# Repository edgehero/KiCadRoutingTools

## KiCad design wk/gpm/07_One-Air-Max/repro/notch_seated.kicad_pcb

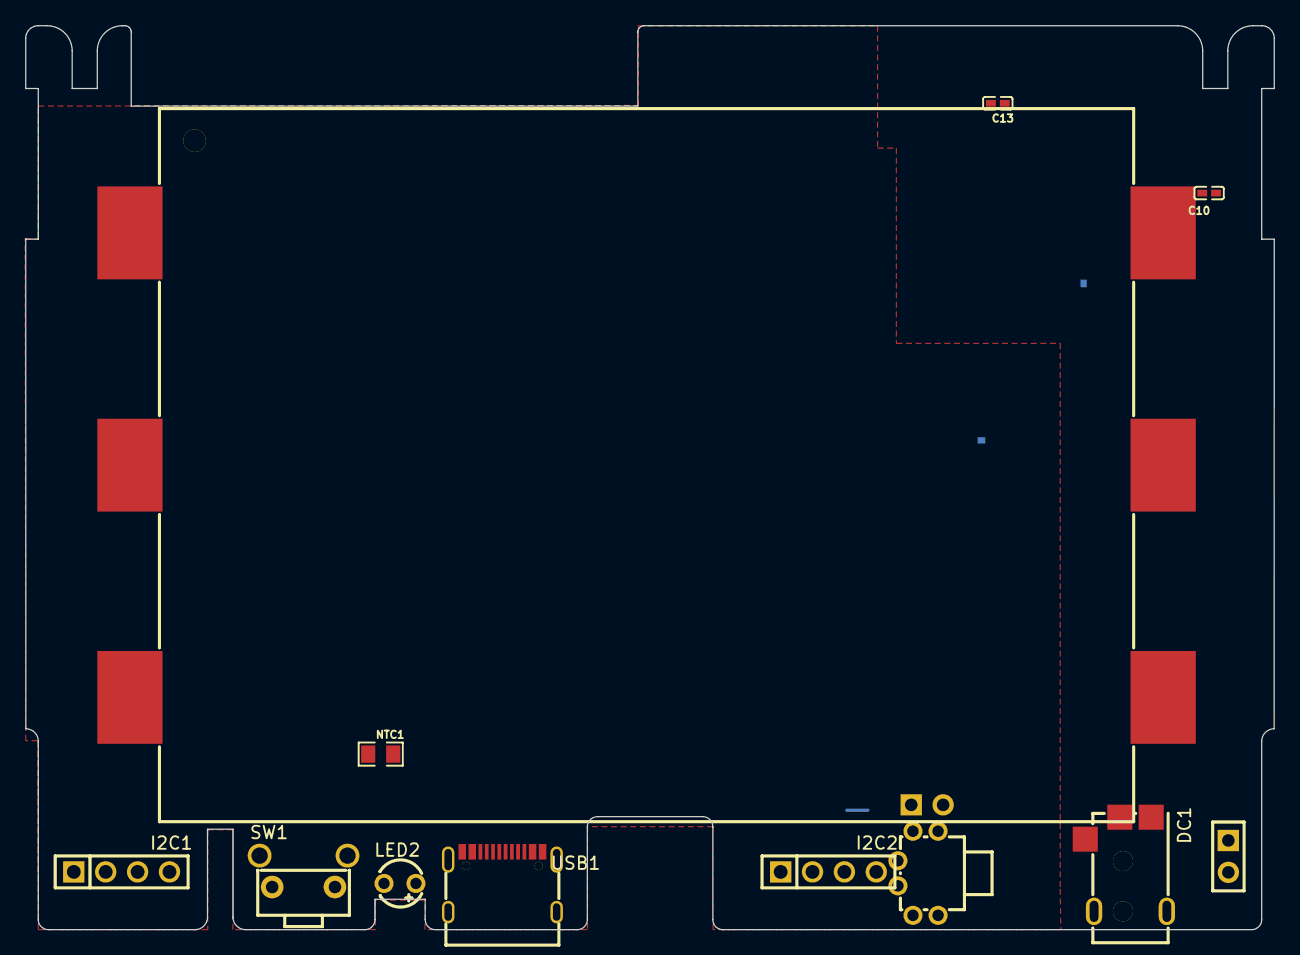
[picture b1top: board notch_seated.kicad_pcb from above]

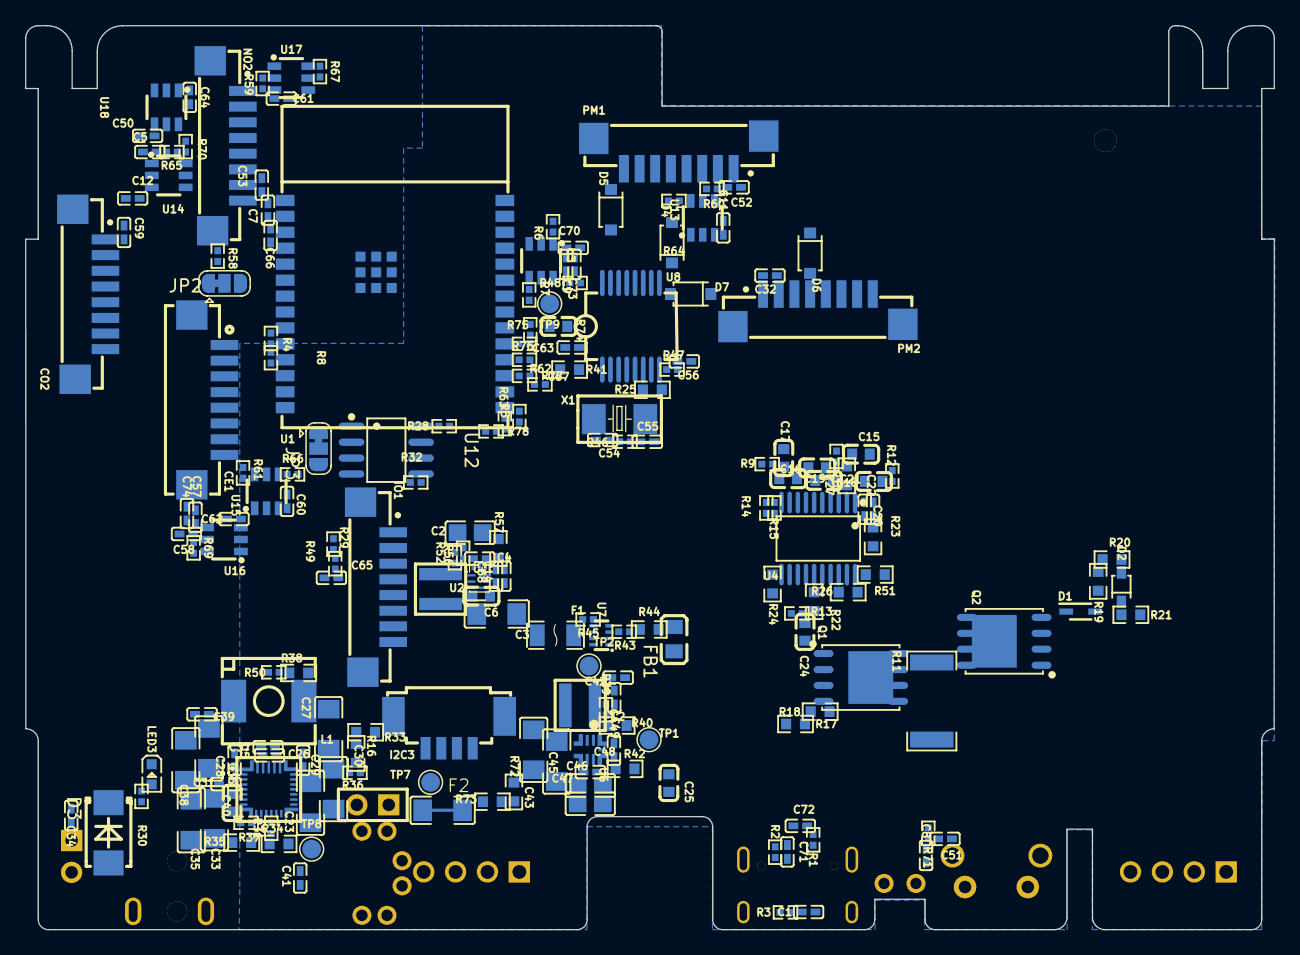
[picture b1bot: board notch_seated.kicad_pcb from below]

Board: 4 copper layers, 99.5 x 72.0 mm, 204 parts (192 on the bottom side), 120 nets, no tracks yet.

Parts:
BAT1: BH-18650-B5BA016; BAT-SMD_BH-18650-B5BA016
Battery1: ZX-PM2.54-1-2PY; HDR-TH_2P-P2.54-V-F
C1, C5, C7, C9, C10, C11, C12, C13, C26, C31, C34, C37, C39, C42, C44, C47, C50, C51, C52, C53, C56, C63, C65, C70: 0.1uF; C0402
C2: 10uF/25V; C0805
C3: 22uF/16V; C1206
C4, C49: 3.3nF; C0402
C6: 22uF; C0603
C8: 10nF; C0402
C14, C57, C58, C68, C74: 22uF; C0402
C15, C16, C17, C18, C19, C21, C24, C25: 0.1uF/50V; C0603
C20, C22: 1uF/50V; C0402
C23, C27, C30, C33, C35, C38, C40, C43, C45: 10uF; C1206
C28, C29: 47nF; C0402
C32, C59, C60, C61, C62, C64: 2.2uF; C0402
C36: 4.7uF; C0603
C41, C71, C72: 1nF; C0402
C46, C48: 22uF; C0805
C54, C55: 22pF_NM; C0402
C66, C73: 1uF; C0402
C67: 500pF; C0603
CE1: HC-1.25-8PWT; CONN-SMD_HC-1.25-8PWT
CO2: HC-1.25-8PLT; CONN-SMD_8P-P1.25_HC-1.25-8PLT
D1: BAS16J_135; SOD2512X80N
D2: MMSZ5246BS-7-F; SOD-323_L1.8-W1.3-LS2.5-RD
D3: SMBJ24A_C908801; SMB_L4.4-W3.6-LS5.3-RD
D4, D5, D6, D7: B5817W_C7420328; SOD-123_L2.7-W1.6-LS3.7-FD
DC1: DC-045A-13A; DC-IN-SMD_DC-045A-13A
F1: 2A-16V; F1206
F2: Fuse 5A; PCB_fuse
FB1: PBY201209T-601Y-N; L0805
I2C1, I2C2: Conn_01x04; HDR-TH_4P-P2.54-V-F
I2C3: 1.25-4PWB; CONN-SMD_1.25-4PWB
IO1: HC-1.25-8PLT; CONN-SMD_8P-P1.25_HC-1.25-8PLT
JP2, JP3: SolderJumper_3_Bridged12; SolderJumper-3_P1.3mm_Bridged12_RoundedPad1.0x1.5mm
L1: SPM6530T-1R0M120; IND-SMD_L7.1-W6.5-P5.60
L2: XGL4020-102MEC; IND-SMD_L4.0-W4.0_XAL4030-332MEC
L3: YSMC0420V-1R0M; IND-SMD_L4.0-W4.0_XGL4020
LED2: XL-304UBC; LED-TH_BD3.8-P2.54-FD_BLUE
LED3: FC-DA1608HRK-620D; LED0603-RD_RED
NO2: HC-1.25-8PLT; CONN-SMD_8P-P1.25_HC-1.25-8PLT
NTC1: KNTC0805/10KF3950; R0805
PM1, PM2: HC-1.25-8PLT; CONN-SMD_8P-P1.25_HC-1.25-8PLT
PWR_SW1: TK-6580A8-1; SW-TH_TK-6580A8-1
Q1, Q2: CSD18534Q5A; PQFN-8_L5.8-W4.9-P1.27-LS6.0-BL
R1, R2, R48: 5.1K; R0402
R3, R6, R31, R37: 100K; R0402
R4, R5, R8, R28, R29, R30, R32, R45, R47, R49, R50, R58, R59, R60, R61, R64, R65, R66, R67, R69, R70, R74, R75, R76, R77, R78: 10K; R0402
R7: 51K; R0402
R9, R12, R14, R15: 1K; R0402
R10, R13, R36: 100; R0402
R11: 10m / 1W; R2512
R16: 10.5K; R0603
R17, R19: 5.1K; R0603
R18: 10M; R0603
R20: 1M; R0603
R21: 3M; R0603
R22: 10K; R0603
R23, R25, R26, R27, R33, R41, R51, R72, R73: 0; R0603
R24: 470K; R0603
R34: 5.23K; R0603
R35: 255K; R0603
R38: 30.1K; R0603
R39: 200K; R0402
R40: 27K; R0603
R42, R57: 7.15K; R0603
R43: 16.9K; R0402
R44: 5K; R0603
R46: 1M; R0402
R52: 113k; R0402
R56: 24.9k; R0402
R62, R63: 22; R0402
R71: 210; R0402
SW1: TS-1096-A1B2-D2; KEY-TH_TS-1096-A1B2-D2
Solarpower1: ZX-PM2.54-1-2PY; HDR-TH_2P-P2.54-V-F
TP1, TP2, TP7, TP8, TP9: T_PG; TestPoint_Pad_D1.5mm
U1: ESP32-C6-WROOM-1-N8; WIRELM-SMD_ESP32-C6-WROOM-1
U2: TPS62902RPJR; VQFN-HR-9_L2.0-W1.5-P0.50-TL
U3: TPL5010DDCR; SOT-23-6_L2.9-W1.6-P0.95-LS2.8-BR
U4: BQ7790512PWR; TSSOP-20_L6.5-W4.4-P0.65-LS6.4-BL
U5: BQ25672RQMR; VQFN-29_L4.0-W4.0-P0.40-BL
U6: TPS62903QRYTRQ1_C20345985; VQFNHR-9_L2.2-W2.0_TPS62993QRYTRQ1
U7: TPS2117DRLR_C22399676; SOT-583-8_L2.1-W1.2-P0.50-LS1.6-BL
U8: WK2132-ISSG; SSOP-16_L7.2-W5.3-P0.65-LS7.8-BL
U12: AT24CM02-SSHD-B; SOIC-8_L4.9-W3.9-P1.27-LS6.0-BL
U13, U14, U15, U16, U17, U18: TPS27081ADDCR; SOT-23-6_L2.9-W1.6-P0.95-LS2.8-BR
USB1: GT-USB-7010ASV; USB-C-SMD_G-SWITCH_GT-USB-7010ASV
X1: SMD-5032_2P 14.7456MHZ 20PF 20PPM; OSC-SMD_L5.0-W3.2

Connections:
+3V3: C3.2, C6.2, C7.2, C9.1, C10.2, C13.2, C53.2, C63.2, C65.2, C66.2, C70.2, C73.2, I2C1.1, I2C2.1, I2C3.1, IO1.3, L3.1, R4.2, R5.2, R6.1, R8.2, R28.2, R29.2, R32.2, R47.2, R48.1, R49.2, R52.2, R66.2, R67.2, R74.2, R75.2, R76.2, R77.2, R78.2, U1.2 (3V3), U2.3 (VOS), U3.1 (VDD), U8.1 (VCC), U12.8 (VCC), U15.4 (VIN), U17.4 (VIN)
+5V: C2.1, C5.2, C14.2, C50.2, C57.2, C58.2, C68.2, C74.2, F1.1, IO1.1, R45.2, R64.2, R65.2, R69.2, R70.2, U2.5 (EN), U2.6 (VIN), U13.4 (VIN), U14.4 (VIN), U16.4 (VIN), U18.4 (VIN)
+5VBAT: C42.2, C43.2, C44.2, C45.2, L2.1, R39.2, U6.3 (VOS), U7.6 (VIN2)
+5VUSB: R43.2, U7.3 (VIN1), U7.5 (MODE), USB1.A4B9 (VBUS), USB1.B4A9 (VBUS)
/A0: R25.1, U8.6 (MP1)
/A1: R41.1, U8.4 (MP3)
/BOOT: C8.2, R5.1, SW1.1, U1.15 (IO9)
/Battery_holder/AVDD: C22.2, R23.2, U4.2 (AVDD)
/Battery_holder/BAT1: BAT1.2, BAT1.4, R9.1
/Battery_holder/BAT2: BAT1.3, BAT1.5, R12.1
/Battery_holder/BAT_TH: NTC1.2, R22.1, U4.15 (TS)
/Battery_holder/CHG: R19.2, U4.13 (CHG)
/Battery_holder/CTRC: R26.1, U4.18 (CTRC)
/Battery_holder/CTRD: R27.2, U4.19 (CTRD)
/Battery_holder/DSG: R17.2, U4.11 (DSG)
/Battery_holder/LD: R24.2, U4.14 (LD)
/Battery_holder/SRN: C17.1, C19.2, R13.2, U4.10 (SRN)
/Battery_holder/SRP: C15.2, C17.2, R10.2, U4.9 (SRP)
/Battery_holder/VBAT+: BAT1.6, C25.2, PWR_SW1.4, PWR_SW1.6, R14.1, R15.1
/EN: C67.2, R6.2, TP9.1, U1.3 (EN), U3.6 (RSTn)
/EN_CE: CE1.5, R61.2, U1.23 (IO15), U15.5 (ON/OFF), U16.5 (ON/OFF)
/EN_CO2: R58.2, U1.5 (IO5), U14.5 (ON/OFF)
/EN_NO2: R59.2, U1.4 (IO4), U17.5 (ON/OFF), U18.5 (ON/OFF)
/EN_PM: R60.2, U1.26 (IO3), U13.5 (ON/OFF)
/I2C_~RST: C56.2, R47.1, U8.8 (#RSTN)
/IO18: IO1.6, R78.1, U1.16 (IO18)
/IO19: IO1.5, R77.1, U1.17 (IO19)
/IO20: IO1.4, R76.1, U1.18 (IO20)
/IO21: CE1.6, R75.1, U1.19 (IO21)
/IO22: R74.1, U1.20 (IO22)
/IO23: CE1.4, R8.1, U1.21 (IO23)
/LED: R71.2, U1.11 (IO10)
/PM1_RXD: D5.2 (K), PM1.5
/PM1_TXD: D4.1 (A), PM1.4
/PM2_RXD: D7.2 (K), PM2.5
/PM2_TXD: D6.1 (A), PM2.4
/PR1: R43.1, R44.2, U7.4 (PR1)
/RX_CE: JP3.1 (A), U1.24 (RXD0)
/RX_CO2: CO2.5, U1.8 (IO0)
/SCL: I2C1.3, I2C2.3, I2C3.3, IO1.7, JP2.3 (B), NO2.7, R28.1, R32.1, U1.6 (IO6), U5.14 (SCL), U8.5 (MP2), U12.6 (SCL)
/SCL_TXD: CE1.7, JP2.2 (C)
/SDA: I2C1.4, I2C2.4, I2C3.4, IO1.8, JP3.3 (B), NO2.8, R29.1, R49.1, U1.7 (IO7), U5.15 (SDA), U8.7 (MP0), U12.5 (SDA)
/SDA_RXD: CE1.8, JP3.2 (C)
/Solar_module/BTST1: C28.2, U5.4 (BTST1)
/Solar_module/BTST2: C29.2, U5.19 (BTST2)
/Solar_module/FB/VSET: R39.1, R40.2, TP2.1, U6.9 (FB/VSET)
/Solar_module/ILIM_HIZ: R35.2, R37.2, U5.17 (ILIM_HIZ)
/Solar_module/PROG: R16.2, U5.20 (PROG)
/Solar_module/REGN: C36.2, R34.1, R35.1, U5.5 (REGN)
/Solar_module/SW1: C28.1, L1.1, U5.28 (SW1)
/Solar_module/SW2: C29.1, L1.2, U5.26 (SW2)
/Solar_module/SYS: C26.2, C27.2, R72.1, TP7.1, U5.25 (SYS)
/Solar_module/Solar+: C31.2, C33.2, C34.2, C35.2, D3.1, DC1.1, R30.1, Solarpower1.1, U5.2 (VBUS), U5.3 (VBUS), U5.8 (VAC2), U5.9 (VAC1)
/Solar_module/VBAT: Battery1.1, C23.2, C30.2, F2.1, R36.2, R73.1, TP8.1, U5.22 (BAT), U5.23 (BAT)
/TX_CE: JP2.1 (A), U1.25 (TXD0)
/TX_CO2: CO2.4, U1.9 (IO1)
/USB+: R63.2, U1.14 (IO13)
/USB-: R62.2, U1.13 (IO12)
/USB_D+: C71.2, R63.1, USB1.A6 (DP1), USB1.B6 (DP2)
/USB_D-: C72.2, R62.1, USB1.A7 (DN1), USB1.B7 (DN2)
/VMUX: F1.2, U7.2 (VOUT), U7.7 (VOUT)
/VOUT1: C11.2, C32.2, C52.2, PM1.1, PM2.1, U13.2 (VOUT), U13.3 (VOUT)
/VOUT2: C12.2, C59.2, CO2.1, U14.2 (VOUT), U14.3 (VOUT)
/VOUT3: C60.2, CE1.3, U15.2 (VOUT), U15.3 (VOUT)
/VOUT4: C62.2, CE1.1, U16.2 (VOUT), U16.3 (VOUT)
/VOUT5: C61.2, NO2.3, U17.2 (VOUT), U17.3 (VOUT)
/VOUT6: C64.2, NO2.1, U18.2 (VOUT), U18.3 (VOUT)
/WD_RST: U1.27 (IO2), U3.4 (DONE)
BAT-: BAT1.1, C15.1, C16.1, C18.1, C19.1, C20.1, C21.1, C22.1, NTC1.1, R10.1, R11.1, R26.2, R27.1, R51.1, U4.8 (AVSS), U4.20 (DVSS)
GND: C1.1, C2.2, C3.1, C4.1, C5.1, C6.1, C7.1, C8.1, C9.2, C10.1, C11.1, C12.1, C13.1, C14.1, C32.1, C50.1, C51.1, C52.1, C53.1, C54.1, C55.1, C56.1, C57.1, C58.1, C59.1, C60.1, C61.1, C62.1, C63.1, C64.1, C65.1, C66.1, C67.1, C68.1, C70.1, C71.1, C72.1, C73.1, C74.1, CE1.2, CE1.9, CE1.10, CO2.2, CO2.10, FB1.1, I2C1.2, I2C2.2, I2C3.2, I2C3.5, IO1.2, IO1.9, IO1.10, LED2.2 (K), NO2.2, NO2.9, NO2.10, PM1.2, PM1.10, PM2.2, PM2.9, PM2.10, R1.1, R2.1, R3.1, R7.1, R25.2, R41.2, R44.1, R56.1, R57.1, R58.1, R59.1, R60.1, R61.1, SW1.2, U1.1 (GND), U1.28 (GND), U1.29 (GND), U1.30 (GND), U1.31 (GND), U1.32 (GND), U1.33 (GND), U1.34 (GND), U1.35 (GND), U1.36 (GND), U1.37 (GND), U2.4 (GND), U3.2 (GND), U7.1 (GND), U8.12 (GND), U8.13 (MD0), U12.3 (A2), U12.4 (GND), U12.7 (WP), U13.1 (R2), U14.1 (R2), U15.1 (R2), U16.1 (R2), U17.1 (R2), U18.1 (R2), USB1.A1B12 (GND), USB1.B1A12 (GND)
unnamed: C1.2, R3.2, USB1.1 (SHELL), USB1.2 (SHELL), USB1.3 (SHELL), USB1.4 (SHELL)
unnamed: C24.2, Q1.1 (S), Q1.2 (S), Q1.3 (S), R11.2, R13.1, R18.1
unnamed: D1.2, R19.1, R20.2
unnamed: D1.1, D2.1 (K), Q2.4 (G), R20.1, R21.2
unnamed: D4.2 (K), U8.15 (TX1)
unnamed: D5.1 (A), U8.16 (RX1)
unnamed: D6.2 (K), U8.10 (TX2)
unnamed: D7.1 (A), U8.11 (RX2)
unnamed: F2.2, PWR_SW1.2, PWR_SW1.5
unnamed: C51.2, LED2.1 (A), R71.1
unnamed: LED3.2 (A), R30.2
unnamed: LED3.1 (K), U5.1 (STAT)
unnamed: Q1.5 (D), Q1.6 (S), Q1.7 (S), Q1.8 (S), Q2.5 (D), Q2.6 (S), Q2.7 (S), Q2.8 (S)
unnamed: Q1.4 (G), R17.1, R18.2
unnamed: R16.1, R33.1
unnamed: R4.1, U1.10 (IO8)
unnamed: R52.1, R56.2, U2.9 (FB/VSET)
unnamed: R57.2, U2.7 (MODE/S-CONF)
unnamed: C4.2, U2.8 (SS/TR)
unnamed: L3.2, U2.2 (SW)
unnamed: R7.2, U3.3 (DELAY/M_RST)
unnamed: R23.1, R51.2, U4.17 (CCFG)
unnamed: C16.2, R9.2, U4.7 (VC1)
unnamed: C18.2, R12.2, U4.6 (VC2)
unnamed: C21.2, R15.2, U4.3 (VC5), U4.4 (VC4), U4.5 (VC3)
unnamed: C20.2, R14.2, U4.1 (VDD)
unnamed: R22.2, U4.16 (VTB)
unnamed: R36.1, U5.18 (BATP)
unnamed: R31.1, U5.13 (CE)
unnamed: C37.2, C38.2, C39.2, C40.2, U5.29 (PMID)
unnamed: C41.1, U5.24 (SDRV)
unnamed: R34.2, R38.1, R50.2, U5.16 (TS)
unnamed: C46.2, C47.2, C48.2, R72.2, R73.2, U6.5 (EN), U6.6 (VIN)
unnamed: R42.2, U6.7 (MODE/S-CONF)
unnamed: TP1.1, U6.1 (PG)
unnamed: C49.2, U6.8 (SS/TR)
unnamed: L2.2, U6.2 (SW)
unnamed: R45.1, U7.8 (ST)
unnamed: R48.2, U8.9 (#IRQ)
unnamed: C54.2, R46.2, U8.2 (OSCI), X1.2 (OSC2)
unnamed: C55.2, R46.1, U8.3 (OSCO), X1.1 (OSC1)
unnamed: R64.1, U13.6 (R1/C1)
unnamed: R65.1, U14.6 (R1/C1)
unnamed: R66.1, U15.6 (R1/C1)
unnamed: R69.1, U16.6 (R1/C1)
unnamed: R67.1, U17.6 (R1/C1)
unnamed: R70.1, U18.6 (R1/C1)
unnamed: R1.2, USB1.A5 (CC1)
unnamed: R2.2, USB1.B5 (CC2)
PGND: Battery1.2, C23.1, C24.1, C25.1, C26.1, C27.1, C30.1, C31.1, C33.1, C34.1, C35.1, C36.1, C37.1, C38.1, C39.1, C40.1, C41.2, C42.1, C43.1, C44.1, C45.1, C46.1, C47.1, C48.1, C49.1, D2.2 (A), D3.2, DC1.2, DC1.3, DC1.4, FB1.2, Q2.1 (S), Q2.2 (S), Q2.3 (S), R21.1, R24.1, R31.2, R33.2, R37.1, R38.2, R40.1, R42.1, R50.1, Solarpower1.2, U5.10 (ACDRV2), U5.11 (ACDRV1), U5.27 (GND), U6.4 (GND)

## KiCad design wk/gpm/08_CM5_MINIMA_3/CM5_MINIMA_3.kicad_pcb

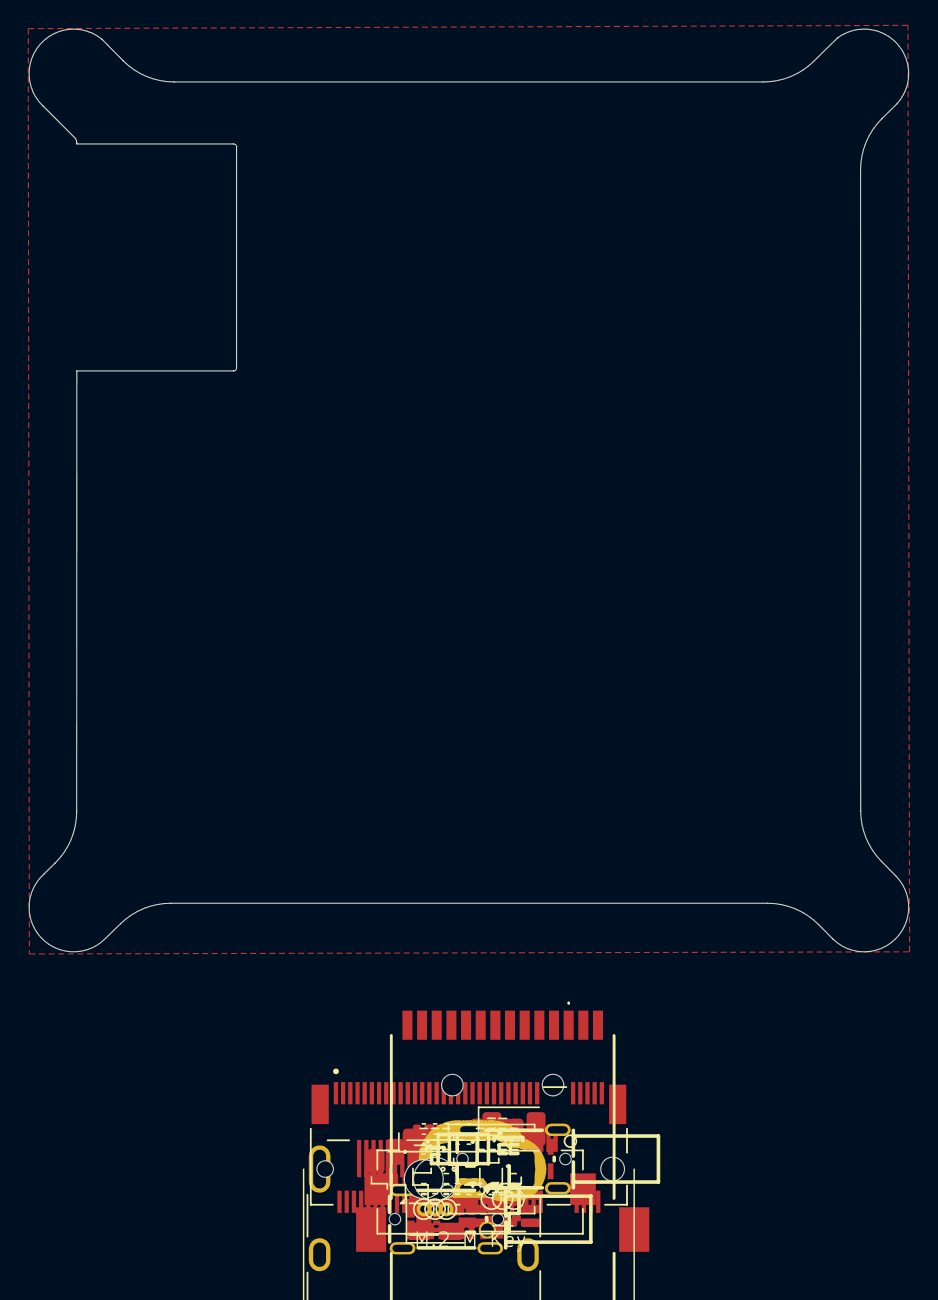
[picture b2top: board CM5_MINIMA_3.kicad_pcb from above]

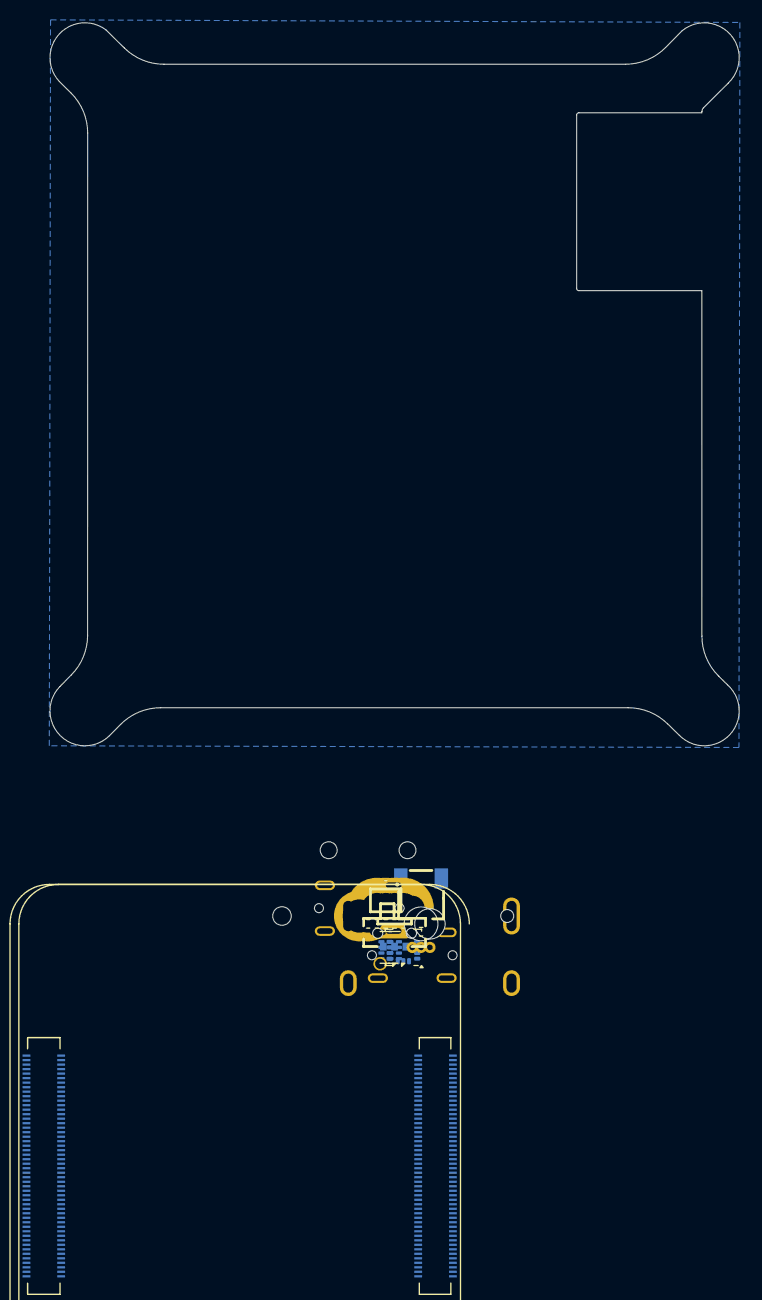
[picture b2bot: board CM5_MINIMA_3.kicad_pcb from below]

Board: 6 copper layers, 61.2 x 64.2 mm, 84 parts (15 on the bottom side), 95 nets, no tracks yet.

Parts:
C101, C102, C401, C501, C502, C503, C706, C712: 100n; C_0402_1005Metric
C601: 4u7; C_0805_2012Metric
C701, C703, C704, C705, C708, C709, C710, C711: 10u; C_0805_2012Metric
C702: 100uF; CP_EIA-3528-21_Kemet-B
C707: 4.7nF; C_0402_1005Metric
CN1: SM02B-SRSS-TB (LF)(SN); CONN-SMD_2P-P1.00_SM02B-SRSS-TB-LF-SN
D101, D502, D701: RCLAMP0502BA; SOT-416
D401, D402, D403: PUSB3F96X; DFN2510A-10_L2.5-W1.0-P0.50-BL
D605, D606, D702: GREEN; LED-SMD_L1.7-W0.6-RD
H101: MountingHole_Pad; MountingHole_2.2mm_M2_DIN965_Pad_TopBottom
H102, H103, H104, H105: MountingHole_Pad; MountingHole_2.7mm_Pad
J1: GLPLX-SMT-188S7; GLPLXSMT188S7QQYG
J101: TYPEC-305-ACP16H458; USB-C-SMD_TYPEC-305-ACP16H458
J501: GT-HD001B-CNNG1; EDAC 690-019-298-412
J502: I2C; JST_SH_BM04B-SRSS-TB_1x04-1MP_P1.00mm_Vertical
J503: SPI; JST_SUR_BM10B-SURS-TF_1x10-1MP_P0.80mm_Vertical
J601: JST_SHBM04B-SRSS-TB; JST_SH_BM04B-SRSS-TB_1x04-1MP_P1.00mm_Vertical
J701: Bus_M.2_Socket_M; M.2 M Key socket_2230_2242
J802: Conn_01x22_Female; Hirose_FH12-22S-0.5SH_1x22-1MP_P0.50mm_Horizontal
L701: 2.2uH; L_Coilcraft_XAL5030-XXX
M701, M702: M.2 Solder Nut; MountingHole_3mm_Pad
Module301: ComputeModule5-CM5; Raspberry-Pi-5-Compute-Module_GPIO
Module302: ComputeModule5-CM5; Raspberry-Pi-5-Compute-Module_HSS
R101, R501, R502, R605, R606, R706, R707: 2k2; R_0402_1005Metric
R102, R103, R403: 0R; R_0402_1005Metric
R104, R107, R108, R705: 10k; R_0402_1005Metric
R401, R402: 470R; R_0402_1005Metric
R701: 15k; R_0402_1005Metric
R702, R703: 22k; R_0402_1005Metric
R704: 100k; R_0402_1005Metric
SW101: MK-11C04-G013; SW-SMD_MK-11C04-G013
SW501: TS-1010A-B; SW-SMD_TS-1010A-B
TP101: VBUS; TestPoint_Pad_D1.0mm
TP102: +5V_PI; TestPoint_Pad_D1.0mm
TP103: +3V3_PI; TestPoint_Pad_D1.0mm
TP104, TP105, TP106: GND; TestPoint_THTPad_D1.0mm_Drill0.5mm
U1: LIS3DH; LGA-16_3x3mm_P0.5mm_LayoutBorder3x5y
U401, U402: TPD4EUSB30; USON-10_2.5x1.0mm_P0.5mm
U405: STMPS2151STR; SOT-23-5
U602: SN74LVC1G14DBVR; SOT-353_SC-70-5
U701: AP22653W6; SOT-23-6
U702: AP3441SHE-7B; DFN-8-1EP_2x2mm_P0.5mm_EP1.05x1.75mm
U703: ASEK-32.768KHZ-L-R-T; Crystal_SMD_3225-4Pin_3.2x2.5mm
USB701: TYPEC-305-ACP16H458; USB-C-SMD_TYPEC-305-ACP16H458

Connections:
+1V8: Module301.88 (+1.8v_(Output)), Module301.90 (+1.8v_(Output)), R103.1
+3V3_PI: C503.1, C601.1, J1.12 (A_GREEN), J1.14 (A_YELLOW), J502.4, J503.1, J802.22, Module301.84 (+3.3v_(Output)), Module301.86 (+3.3v_(Output)), R102.1, R107.2, R501.1, R502.1, TP103.1, U1.1 (VDD_IO), U1.14 (VDD)
+5V: C101.1, C102.1, C501.1, C701.1, C704.1, C705.1, C706.1, D605.2 (A), D606.2 (A), J101.A4 (VBUS), J101.A9 (VBUS), J101.B4 (VBUS), J101.B9 (VBUS), J601.1, Module301.77 (+5v_(Input)), Module301.79 (+5v_(Input)), Module301.81 (+5v_(Input)), Module301.83 (+5v_(Input)), Module301.85 (+5v_(Input)), Module301.87 (+5v_(Input)), R101.1, R702.2, R703.2, TP101.1, TP102.1, U405.4 (EN), U405.5 (VIN), U602.5 (VCC), U701.1 (IN), U702.3 (VIN)
+BATT: CN1.1, Module301.76 (VBAT)
/CC1: J101.A5 (CC1), Module301.94 (CC1)
/CC2: J101.B5 (CC2), Module301.96 (CC2)
/CM5/BL_GPIO24: J503.7, Module301.45 (GPIO24)
/CM5/CAM_GPIO0: J802.17, Module301.97 (CAM_GPIO0)
/CM5/CAM_GPIO1: J802.18, Module301.100 (CAM_GPIO1)
/CM5/CS_GPIO18: J503.5, Module301.49 (GPIO18)
/CM5/DC_GPI25: J503.3, Module301.41 (GPIO25)
/CM5/DPHY0_P.C_N: J802.8, Module302.127 (MIPI0_C_N)
/CM5/DPHY0_P.C_P: J802.9, Module302.129 (MIPI0_C_P)
/CM5/DPHY0_P.D0_N: J802.2, Module302.115 (MIPI0_D0_N)
/CM5/DPHY0_P.D0_P: J802.3, Module302.117 (MIPI0_D0_P)
/CM5/DPHY0_P.D1_N: J802.5, Module302.121 (MIPI0_D1_N)
/CM5/DPHY0_P.D1_P: J802.6, Module302.123 (MIPI0_D1_P)
/CM5/DPHY0_P.D2_N: J802.11, Module302.133 (MIPI0_D2_N)
/CM5/DPHY0_P.D2_P: J802.12, Module302.135 (MIPI0_D2_P)
/CM5/DPHY0_P.D3_N: J802.14, Module302.139 (MIPI0_D3_N)
/CM5/DPHY0_P.D3_P: J802.15, Module302.141 (MIPI0_D3_P)
/CM5/EEPROM_nWP: Module301.20 (EEPROM_nWP), R104.2
/CM5/ETH_PI.TRD0_N: J1.3 (TD1-), Module301.10 (Ethernet_Pair0_N), U401.2 (D1-), U401.9
/CM5/ETH_PI.TRD0_P: J1.2 (TD1+), Module301.12 (Ethernet_Pair0_P), U401.1 (D1+), U401.10
/CM5/ETH_PI.TRD1_N: J1.5 (TD2-), Module301.6 (Ethernet_Pair1_N), U401.5 (D2-), U401.6
/CM5/ETH_PI.TRD1_P: J1.4 (TD2+), Module301.4 (Ethernet_Pair1_P), U401.4 (D2+), U401.7
/CM5/ETH_PI.TRD2_N: J1.7 (TD3-), Module301.9 (Ethernet_Pair2_N), U402.2 (D1-), U402.9
/CM5/ETH_PI.TRD2_P: J1.6 (TD3+), Module301.11 (Ethernet_Pair2_P), U402.1 (D1+), U402.10
/CM5/ETH_PI.TRD3_N: J1.9 (TD4-), Module301.5 (Ethernet_Pair3_N), U402.5 (D2-), U402.6
/CM5/ETH_PI.TRD3_P: J1.8 (TD4+), Module301.3 (Ethernet_Pair3_P), U402.4 (D2+), U402.7
/CM5/ETH_nLED_ACTIVITY: Module301.15 (Ethernet_nLED3(3.3v)), R401.1
/CM5/GPIO_VREF: Module301.78 (GPIO_VREF(1.8v/3.3v_Input)), R102.2, R103.2
/CM5/HDMI_PI.CEC: D403.1 (CH1), D403.10 (NC), J501.13 (CEC), Module302.151 (HDMI0_CEC)
/CM5/HDMI_PI.CK_N: D401.5 (CH4), D401.6 (NC), J501.12 (CK-), Module302.190 (HDMI0_CLK_N)
/CM5/HDMI_PI.CK_P: D401.4 (CH3), D401.7 (NC), J501.10 (CK+), Module302.188 (HDMI0_CLK_P)
/CM5/HDMI_PI.D0_N: D401.2 (CH2), D401.9 (NC), J501.9 (D0-), Module302.184 (HDMI0_TX0_N)
/CM5/HDMI_PI.D0_P: D401.1 (CH1), D401.10 (NC), J501.7 (D0+), Module302.182 (HDMI0_TX0_P)
/CM5/HDMI_PI.D1_N: D402.5 (CH4), D402.6 (NC), J501.6 (D1-), Module302.178 (HDMI0_TX1_N)
/CM5/HDMI_PI.D1_P: D402.4 (CH3), D402.7 (NC), J501.4 (D1+), Module302.176 (HDMI0_TX1_P)
/CM5/HDMI_PI.D2_N: D402.2 (CH2), D402.9 (NC), J501.3 (D2-), Module302.172 (HDMI0_TX2_N)
/CM5/HDMI_PI.D2_P: D402.1 (CH1), D402.10 (NC), J501.1 (D2+), Module302.170 (HDMI0_TX2_P)
/CM5/HDMI_PI.HOTPLUG: D403.2 (CH2), D403.9 (NC), J501.19 (HPD/HEAC-), Module302.153 (HDMI0_HOTPLUG)
/CM5/HDMI_PI.SCL: D403.5 (CH4), D403.6 (NC), J501.15 (SCL), Module302.200 (HDMI0_SCL)
/CM5/HDMI_PI.SDA: D403.4 (CH3), D403.7 (NC), J501.16 (SDA), Module302.199 (HDMI0_SDA)
/CM5/MISO_GPIO19: J503.10, Module301.26 (GPIO19)
/CM5/MOSI_GPIO20: J503.9, Module301.27 (GPIO20)
/CM5/PCIE_PI.CLK_N: J701.53 (REFCLKn), Module302.112 (PCIe_CLK_N)
/CM5/PCIE_PI.CLK_P: J701.55 (REFCLKp), Module302.110 (PCIe_CLK_P)
/CM5/PCIE_PI.PWR_EN: Module302.106 (PCIE_PWR_EN), R704.1, U702.7 (EN)
/CM5/PCIE_PI.RX_N: J701.43 (PETp0), Module302.118 (PCIe_RX_N)
/CM5/PCIE_PI.RX_P: J701.41 (PETn0), Module302.116 (PCIe_RX_P)
/CM5/PCIE_PI.TX_N: J701.49 (PERp0), Module302.124 (PCIe_TX_N)
/CM5/PCIE_PI.TX_P: J701.47 (PERn0), Module302.122 (PCIe_TX_P)
/CM5/PCIE_PI.nCLKREQ: J701.52 (~CLKREQ), Module302.102 (PCIe_nCLKREQ)
/CM5/PCIE_PI.nRST: J701.50 (~PERST), Module302.109 (PCIe_nRST)
/CM5/PCIE_PI.nWAKE: J701.54 (~PEWAKE), Module302.104 (PCIE_nWAKE)
/CM5/PI_nLED_PWR: Module301.95 (LED_nPWR), U602.2
/CM5/PWM: J601.2, Module301.19 (FAN_PWM)
/CM5/PWR_BUT: Module301.92 (PWR_BUT), SW501.1
/CM5/RST_GPIO27: J503.4, Module301.48 (GPIO27)
/CM5/SCL0: J802.20, Module301.80 (SCL0)
/CM5/SCLK_GPIO21: J503.8, Module301.25 (GPIO21)
/CM5/SDA0: J802.21, Module301.82 (SDA0)
/CM5/TACHO: J601.4, Module301.16 (FAN_TACHO)
/CM5/USB2P.D_N: D701.2 (K2), Module302.136 (USB3-0-D_N), USB701.A7 (D-), USB701.B7 (D-)
/CM5/USB2P.D_P: D701.1 (K1), Module302.134 (USB3-0-D_P), USB701.A6 (D+), USB701.B6 (D+)
/CM5/VBUS_EN: Module302.111 (VBUS_EN), U701.3 (EN)
/CM5/nLED_ACTIVITY: Module301.21 (LED_nACT), R606.2
/CM5/nLED_SPEED_100_1000: Module301.17 (Ethernet_nLED2(3.3v)), R402.1
/CM5/nRPIBOOT: Module301.93 (nRPIBOOT), SW101.C
/IO/SCL: D502.1 (K1), J502.2, Module301.56 (GPIO3), R502.2, U1.4 (SPC)
/IO/SDA: D502.2 (K2), J502.1, Module301.58 (GPIO2), R501.2, U1.6 (SDI)
/PCIe-M2/FB: C707.2, R705.2, R706.1, U702.1 (FB)
/PCIe-M2/M2_LX: L701.1, U702.6 (LX)
/USB/CC1: R703.1, USB701.A5 (CC1)
/USB/CC2: R702.1, USB701.B5 (CC2)
/USB_C.D_N: D101.2 (K2), J101.A7 (D-), J101.B7 (D-), Module302.103 (USB2_N)
/USB_C.D_P: D101.1 (K1), J101.A6 (D+), J101.B6 (D+), Module302.105 (USB2_P)
GND: C101.2, C102.2, C401.2, C501.2, C502.2, C503.2, C601.2, C701.2, C702.2, C703.2, C704.2, C705.2, C706.2, C708.2, C709.2, C710.2, C711.2, C712.2, CN1.2, D101.3 (A), D401.3 (GND), D401.8 (GND), D402.3 (GND), D402.8 (GND), D403.3 (GND), D403.8 (GND), D502.3 (A), D701.3 (A), H101.1, H102.1, H103.1, H104.1, H105.1, J1.10 (GND), J101.1 (SHIELD), J101.A1 (GND), J101.A12 (GND), J101.B1 (GND), J101.B12 (GND), J501.2 (D2S), J501.5 (D1S), J501.8 (D0S), J501.11 (CKS), J501.17 (GND), J501.SH1 (SH), J501.SH2 (SH), J501.SH3 (SH), J501.SH4 (SH), J502.3, J503.2, J503.6, J601.3, J701.1 (GND), J701.3 (GND), J701.9 (GND), J701.15 (GND), J701.21 (GND), J701.27 (GND), J701.33 (GND), J701.39 (GND), J701.45 (GND), J701.51 (GND), J701.57 (GND), J701.71 (GND), J701.73 (GND), J701.75 (GND), J701.S1, J701.S2, J802.1, J802.4, J802.7, J802.10, J802.13, J802.16, J802.19, Module301.1 (GND), Module301.2 (GND), Module301.7 (GND), Module301.8 (GND), Module301.13 (GND), Module301.14 (GND), Module301.22 (GND), Module301.23 (GND), Module301.32 (GND), Module301.33 (GND), Module301.42 (GND), Module301.43 (GND), Module301.52 (GND), Module301.53 (GND), Module301.59 (GND), Module301.60 (GND), Module301.65 (GND), Module301.66 (GND), Module301.71 (GND), Module301.74 (GND), Module301.98 (GND), Module302.107 (GND), Module302.108 (GND), Module302.113 (GND), Module302.114 (GND), Module302.119 (GND), Module302.120 (GND), Module302.125 (GND), Module302.126 (GND), Module302.131 (GND), Module302.132 (GND), Module302.137 (GND), Module302.138 (GND), Module302.144 (GND), Module302.150 (GND), Module302.155 (GND), Module302.156 (GND), Module302.161 (GND), Module302.162 (GND), Module302.167 (GND), Module302.168 (GND), Module302.173 (GND), Module302.174 (GND), Module302.179 (GND), Module302.180 (GND), Module302.185 (GND), Module302.186 (GND), Module302.191 (GND), Module302.192 (GND), Module302.197 (GND), Module302.198 (GND), R101.2, R104.1, R108.1, R403.2, R701.2, R704.2, R706.2, SW101.1, SW101.4, SW101.5, SW501.2, SW501.3, SW501.4, SW501.5, TP104.1, TP105.1, TP106.1, U1.5 (GND), U1.10 (RES), U1.12 (GND), U401.3 (GND), U401.8 (GND), U402.3 (GND), U402.8 (GND), U405.2 (GND), U602.3 (GND), U701.2 (GND), U702.4 (PGND), U702.8 (SGND), U702.9 (PAD), U703.2 (GND), USB701.1 (EP), USB701.A1 (GND), USB701.A12 (GND), USB701.B1 (GND), USB701.B12 (GND)
HDMI_+5V: C502.1, J501.18 (+5V), U405.1 (VOUT)
M2_3V3: C707.1, C708.1, C709.1, C710.1, C711.1, C712.1, D702.2 (A), J701.2 (3.3V), J701.4 (3.3V), J701.12 (3.3V), J701.14 (3.3V), J701.16 (3.3V), J701.18 (3.3V), J701.70 (3.3V), J701.72 (3.3V), J701.74 (3.3V), L701.2, R705.1, U703.1 (EN), U703.4 (VDD)
unnamed: D605.1 (K), R605.1
unnamed: D606.1 (K), R606.1
unnamed: D702.1 (K), R707.1
unnamed: J1.11 (K_GREEN), R401.2
unnamed: J1.13 (K_YELLOW), R402.2
unnamed: J1.15 (MP1), J1.16 (MP2), R403.1
unnamed: C401.1, J1.1 (VCC)
unnamed: J701.10 (DAS/~DSS/~LED1), R707.2
unnamed: J701.68 (SUSCLK), U703.3 (Out)
unnamed: R605.2, U602.4
unnamed: R107.1, U1.8 (CS)
unnamed: R108.2, U1.7 (SDO)
unnamed: R701.1, U701.5 (ILIM)
VBUS_USB2.0: C702.1, C703.1, U701.6 (OUT), USB701.A4 (VBUS), USB701.A9 (VBUS), USB701.B4 (VBUS), USB701.B9 (VBUS)
